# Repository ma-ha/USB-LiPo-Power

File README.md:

Der IP5306 ist ideal um meine Elektronik Schaltungen mit 5 V zu versorgen.
Über USB-C lädt er einen LiPo Akku mit 2,1 A und wenn kein USB Kabel dran ist, 
versorgt der eingebaut Boost Converter meine Schaltung über Akku.

Diese kleine Platine kommt mit recht wenigen Bauteilen aus. 

Achtet auf den Taster, dass Du den hast, oder ersetze ihn durch was passendes.

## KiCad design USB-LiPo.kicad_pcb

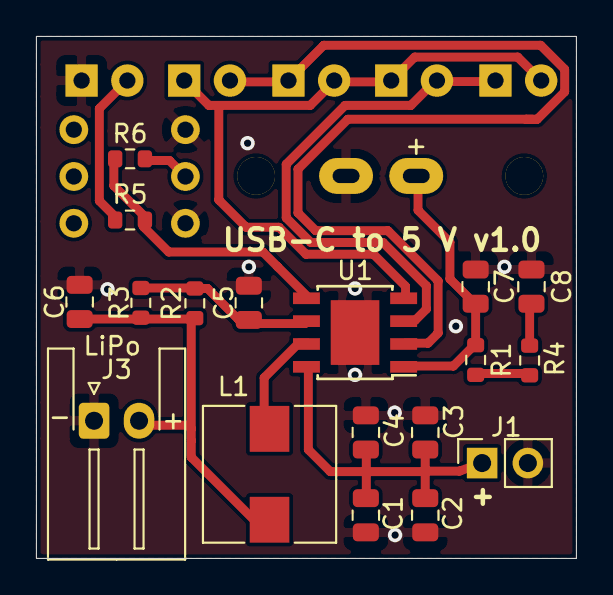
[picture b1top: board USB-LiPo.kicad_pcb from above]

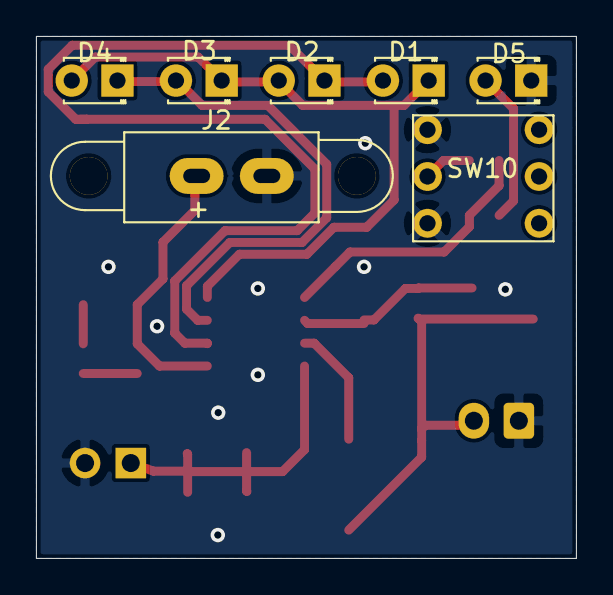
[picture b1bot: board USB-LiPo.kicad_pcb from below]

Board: 2 copper layers, 30.0 x 29.0 mm, 25 parts (7 on the bottom side), 13 nets.

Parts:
C1, C2, C3, C4, C5, C6: 22u; C_0805_2012Metric
C7, C8: 10u; C_0805_2012Metric
D1: 25%; LED_D1.8mm_W3.3mm_H2.4mm
D2: 50%; LED_D1.8mm_W3.3mm_H2.4mm
D3: 75%; LED_D1.8mm_W3.3mm_H2.4mm
D4: 100%; LED_D1.8mm_W3.3mm_H2.4mm
D5: Torch; LED_D1.8mm_W3.3mm_H2.4mm
J1: 5V; PinSocket_1x02_P2.54mm_Vertical
J2: USB-C; USB_C_Charge
J3: LiPo; JST_XH_S2B-XH-A-1_1x02_P2.50mm_Horizontal
L1: 1uH; L_Wuerth_HCM-7070
R1, R2, R3, R4: 1; R_0603_1608Metric
R5: 20; R_0603_1608Metric
R6: 10k; R_0603_1608Metric
SW10: BtnR; PushBtn6x6
U1: IP5306; Diodes_PSOP-8

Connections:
GNDS: C1.1, C2.1, C3.1, C4.1, C5.1, C6.2, C7.2, C8.1, D5.1, J1.2, J2.2, J3.1, SW10.1, SW10.3, U1.9
unnamed: C1.2, C2.2, C3.2, C4.2, J1.1, U1.8
unnamed: C5.2, R2.2, R3.2, U1.6
unnamed: C6.1, J3.2, L1.2, R2.1, R3.1
unnamed: C7.1, J2.1, R1.1, U1.1
unnamed: C8.2, R4.2
unnamed: D1.1, D2.2, D3.1, D4.2, U1.4
unnamed: D1.2, D2.1, U1.2
unnamed: D3.2, D4.1, U1.3
unnamed: D5.2, R5.1
unnamed: L1.1, U1.7
unnamed: R1.2, R4.1
unnamed: R5.2, R6.2, U1.5

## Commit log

2024-12-17 docu
